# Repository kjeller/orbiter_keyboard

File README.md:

# Orbiter Keyboard

A 52-key split keyboard.

!!DISCLAIMER!! There are issues with v1.00 that needs manual patching:
- BOOT0 logic is reversed which makes device always go into DFU mode, R6 needs to be connected to GND
- USB-C CC pin pull-up is common, which makes the USB cable one-way, CC1 and CC2 each needs a 5.1k pull-down resistor

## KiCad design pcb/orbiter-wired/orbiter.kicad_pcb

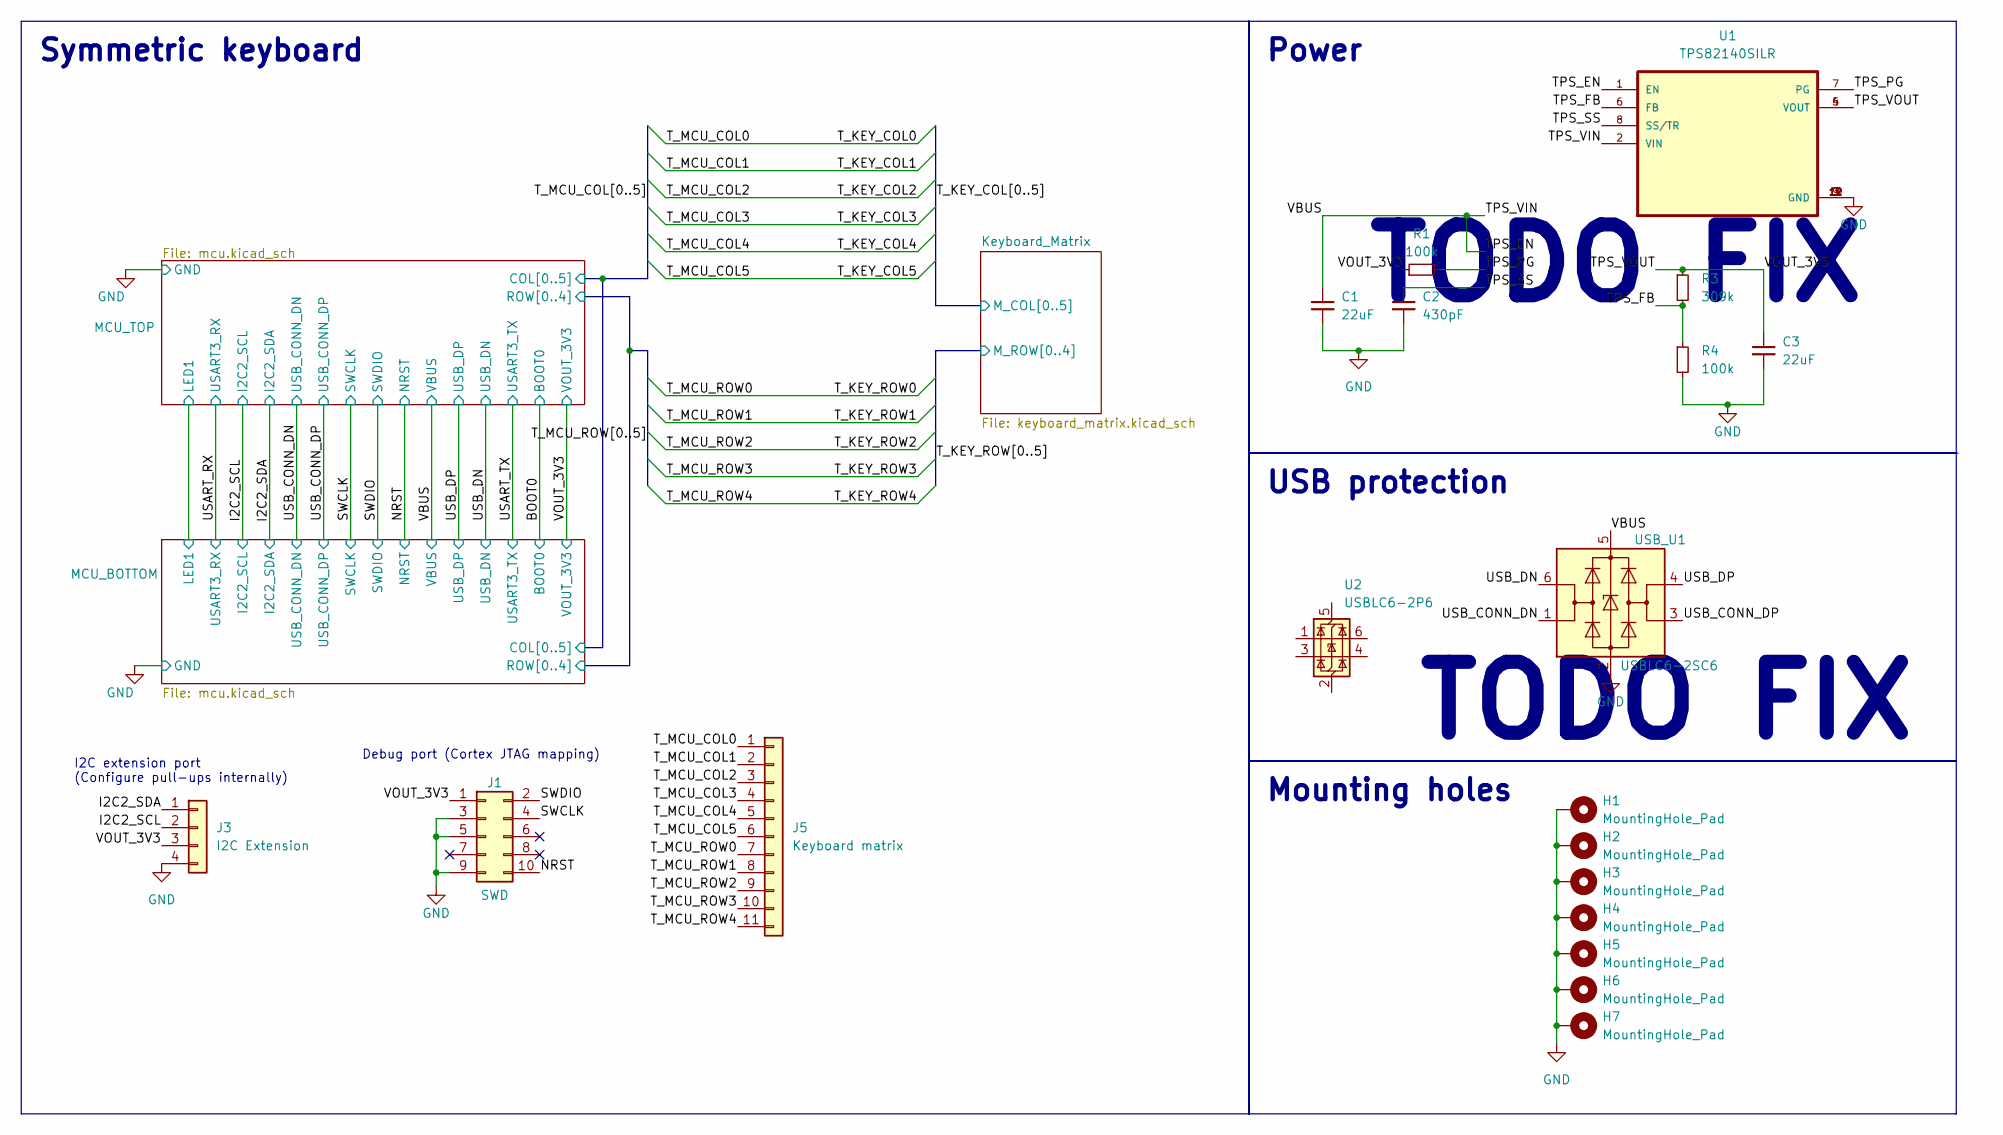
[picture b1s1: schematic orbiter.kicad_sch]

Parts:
C1, C3: 22uF; C_0603_1608Metric_Pad1.08x0.95mm_HandSolder; LCSC C59461
C2: 430pF; C_0603_1608Metric_Pad1.08x0.95mm_HandSolder; LCSC C1620
H1, H2, H3, H4, H5, H6, H7: MountingHole_Pad; MountingHole_2.7mm_M2.5_DIN965_Pad_reversible
J1: SWD; PinSocket_2x05_P2.54mm_Vertical
J3: I2C Extension; PinSocket_1x04_P2.54mm_Vertical
J5: Keyboard matrix; PinSocket_1x11_P2.54mm_Vertical
R1, R4: 100k; R_0603_1608Metric; LCSC C25803
R3: 309k; R_0603_1608Metric; LCSC C23024
U1: TPS82140SILR; LCSC C544385
U2: USBLC6-2P6; SOT-666
USB_U1: USBLC6-2SC6; SOT-23-6; LCSC C2687116

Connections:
/I2C2_SCL: J3.2; also elsewhere on the board
/I2C2_SDA: J3.1; also elsewhere on the board
/NRST: J1.10; also elsewhere on the board
/SWCLK: J1.4; also elsewhere on the board
/SWDIO: J1.2; also elsewhere on the board
/TPS_EN: C1.1, U1.1 (EN), U1.2 (VIN), USB_U1.5 (VBUS); also elsewhere on the board
/TPS_FB: R3.2, R4.1, U1.6 (FB)
/TPS_PG: R1.2, U1.7 (PG)
/TPS_SS: C2.1, U1.8 (SS/TR)
/TPS_VOUT: C3.1, J1.1, J3.3, R1.1, R3.1, U1.4 (VOUT), U1.5 (VOUT); also elsewhere on the board
/T_KEY_COL0: J5.1; also elsewhere on the board
/T_KEY_COL1: J5.2; also elsewhere on the board
/T_KEY_COL2: J5.3; also elsewhere on the board
/T_KEY_COL3: J5.4; also elsewhere on the board
/T_KEY_COL4: J5.5; also elsewhere on the board
/T_KEY_COL5: J5.6; also elsewhere on the board
/T_KEY_ROW0: J5.7; also elsewhere on the board
/T_KEY_ROW1: J5.8; also elsewhere on the board
/T_KEY_ROW2: J5.9; also elsewhere on the board
/T_KEY_ROW3: J5.10; also elsewhere on the board
/T_KEY_ROW4: J5.11; also elsewhere on the board
/USB_CONN_DN: USB_U1.1 (I/O1); also elsewhere on the board
/USB_CONN_DP: USB_U1.3 (I/O2); also elsewhere on the board
/USB_DN: USB_U1.6 (I/O1); also elsewhere on the board
/USB_DP: USB_U1.4 (I/O2); also elsewhere on the board
GND: C1.2, C2.2, C3.2, H1.1, H2.1, H3.1, H4.1, H5.1, H6.1, H7.1, J1.3, J1.5, J1.9, J3.4, R4.2, U1.3 (GND), U1.9 (GND), U1.10 (GND), U1.11 (GND), U1.12 (GND), USB_U1.2 (GND); also elsewhere on the board

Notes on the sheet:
TODO FIX
I2C extension port (Configure pull-ups internally)
Debug port (Cortex JTAG mapping)
Power
Symmetric keyboard
Mounting holes
USB protection

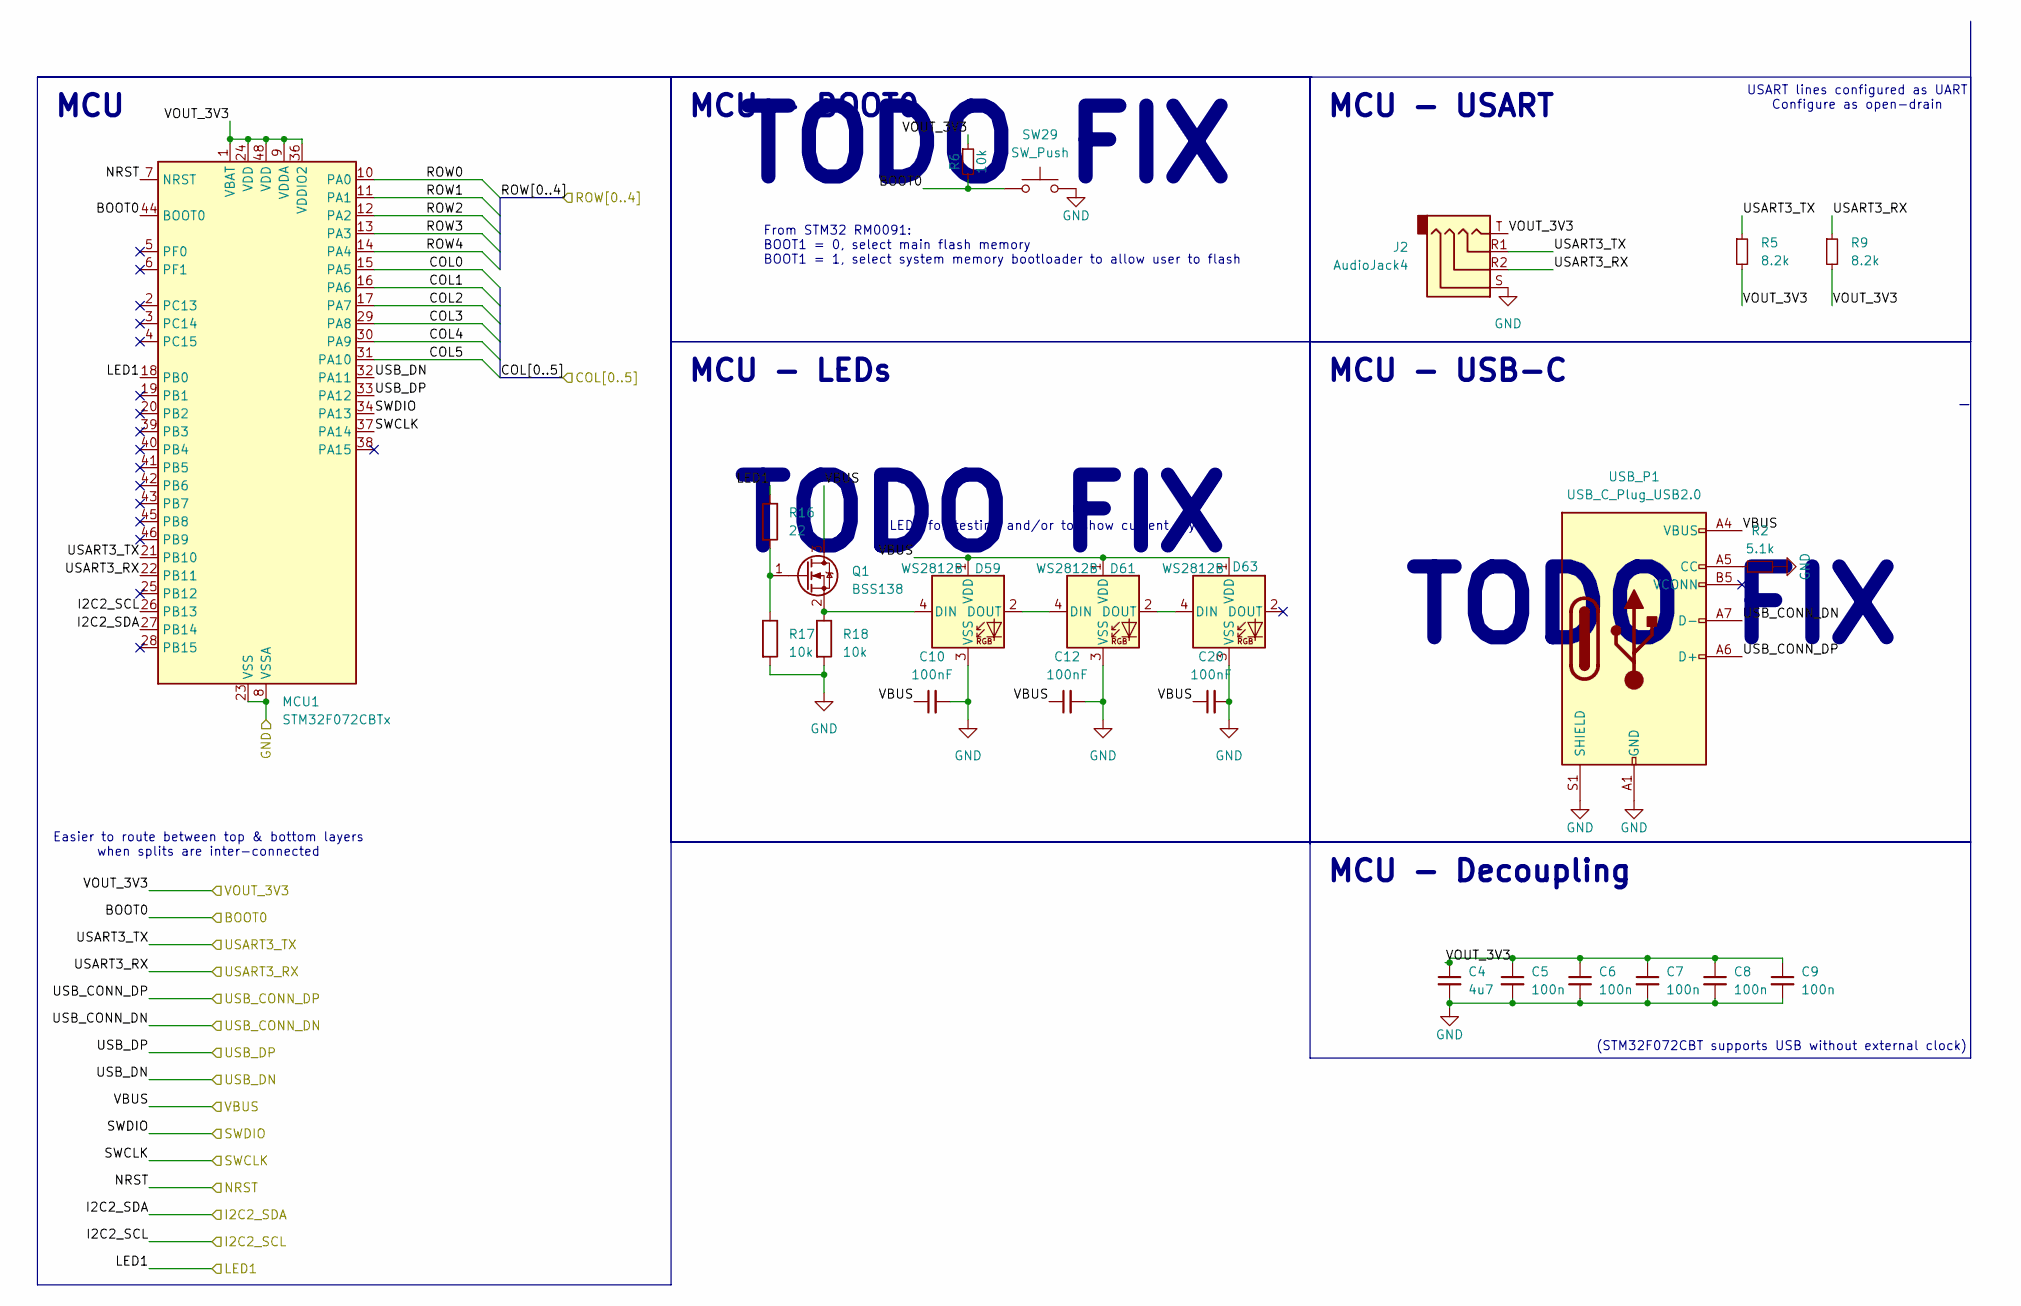
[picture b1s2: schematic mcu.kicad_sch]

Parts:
C4: 4u7; C_0603_1608Metric_Pad1.08x0.95mm_HandSolder
C5, C6, C7, C8, C9: 100n; C_0603_1608Metric_Pad1.08x0.95mm_HandSolder
C10, C12, C20: 100nF; C_0603_1608Metric_Pad1.08x0.95mm_HandSolder
D59, D61, D63: WS2812B; LED_WS2812B-2020_PLCC4_2.0x2.0mm
J2: AudioJack4; Jack_3.5mm_PJ320D_Horizontal
MCU1: STM32F072CBTx; LQFP-48_7x7mm_P0.5mm
Q1: BSS138; SOT-23; MPN BSS138
R2: 5.1k; R_0603_1608Metric
R5, R9: 8.2k; R_0603_1608Metric
R6, R17, R18: 10k; R_0603_1608Metric
R16: 22; R_0603_1608Metric
SW29: SW_Push; SW_SPST_PTS647_Sx38
USB_P1: USB_C_Plug_USB2.0; USB_C_Receptacle_XKB_U262-16XN-4BVC11

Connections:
/BOOT0: MCU1.44 (BOOT0), R6.2, SW29.1; also elsewhere on the board
/I2C2_SCL: MCU1.26 (PB13); also elsewhere on the board
/I2C2_SDA: MCU1.27 (PB14); also elsewhere on the board
/MCU_BOTTOM/LED1: MCU1.18 (PB0), R16.1; also elsewhere on the board
/NRST: MCU1.7 (NRST); also elsewhere on the board
/SWCLK: MCU1.37 (PA14); also elsewhere on the board
/SWDIO: MCU1.34 (PA13); also elsewhere on the board
/TPS_EN: C10.1, C12.1, C20.1, D59.1 (VDD), D61.1 (VDD), D63.1 (VDD), Q1.3 (D), USB_P1.A4 (VBUS), USB_P1.A9 (VBUS), USB_P1.B4 (VBUS), USB_P1.B9 (VBUS); also elsewhere on the board
/TPS_VOUT: C4.1, C5.1, C6.1, C7.1, C8.1, C9.1, J2.T, MCU1.1 (VBAT), MCU1.9 (VDDA), MCU1.24 (VDD), MCU1.36 (VDDIO2), MCU1.48 (VDD), R5.2, R6.1, R9.2; also elsewhere on the board
/T_KEY_COL0: MCU1.15 (PA5); also elsewhere on the board
/T_KEY_COL1: MCU1.16 (PA6); also elsewhere on the board
/T_KEY_COL2: MCU1.17 (PA7); also elsewhere on the board
/T_KEY_COL3: MCU1.29 (PA8); also elsewhere on the board
/T_KEY_COL4: MCU1.30 (PA9); also elsewhere on the board
/T_KEY_COL5: MCU1.31 (PA10); also elsewhere on the board
/T_KEY_ROW0: MCU1.10 (PA0); also elsewhere on the board
/T_KEY_ROW1: MCU1.11 (PA1); also elsewhere on the board
/T_KEY_ROW2: MCU1.12 (PA2); also elsewhere on the board
/T_KEY_ROW3: MCU1.13 (PA3); also elsewhere on the board
/T_KEY_ROW4: MCU1.14 (PA4); also elsewhere on the board
/USART_RX: J2.R2, MCU1.22 (PB11), R9.1; also elsewhere on the board
/USART_TX: J2.R1, MCU1.21 (PB10), R5.1; also elsewhere on the board
/USB_CONN_DN: USB_P1.A7 (D-); also elsewhere on the board
/USB_CONN_DP: USB_P1.A6 (D+); also elsewhere on the board
/USB_DN: MCU1.32 (PA11); also elsewhere on the board
/USB_DP: MCU1.33 (PA12); also elsewhere on the board
GND: C4.2, C5.2, C6.2, C7.2, C8.2, C9.2, C10.2, C12.2, C20.2, D59.3 (VSS), D61.3 (VSS), D63.3 (VSS), J2.S, MCU1.8 (VSSA), MCU1.23 (VSS), MCU1.35 (VSS), MCU1.47 (VSS), R2.2, R17.2, R18.2, SW29.2, USB_P1.A1 (GND), USB_P1.A12 (GND), USB_P1.B1 (GND), USB_P1.B12 (GND), USB_P1.S1 (SHIELD); also elsewhere on the board
unnamed: D59.4 (DIN), Q1.2 (S), R18.1
unnamed: D59.2 (DOUT), D61.4 (DIN)
unnamed: D61.2 (DOUT), D63.4 (DIN)
unnamed: Q1.1 (G), R16.2, R17.1
unnamed: R2.1, USB_P1.A5 (CC)

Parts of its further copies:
C11, C19, C21: 100nF; C_0603_1608Metric_Pad1.08x0.95mm_HandSolder
C13: 4u7; C_0603_1608Metric_Pad1.08x0.95mm_HandSolder
C14, C15, C16, C17, C18: 100n; C_0603_1608Metric_Pad1.08x0.95mm_HandSolder
D60, D62, D64: WS2812B; LED_WS2812B-2020_PLCC4_2.0x2.0mm
J4: AudioJack4; Jack_3.5mm_PJ320D_Horizontal
MCU2: STM32F072CBTx; LQFP-48_7x7mm_P0.5mm
Q2: BSS138; SOT-23; MPN BSS138
R7, R20, R21: 10k; R_0603_1608Metric
R8: 5.1k; R_0603_1608Metric
R10, R11: 8.2k; R_0603_1608Metric
R19: 22; R_0603_1608Metric
SW30: SW_Push; SW_SPST_PTS647_Sx38
USB_P2: USB_C_Plug_USB2.0; USB_C_Receptacle_XKB_U262-16XN-4BVC11

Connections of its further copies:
/BOOT0: MCU2.44 (BOOT0), R7.2, SW30.1; also elsewhere on the board
/I2C2_SCL: MCU2.26 (PB13); also elsewhere on the board
/I2C2_SDA: MCU2.27 (PB14); also elsewhere on the board
/MCU_BOTTOM/LED1: MCU2.18 (PB0), R19.1; also elsewhere on the board
/NRST: MCU2.7 (NRST); also elsewhere on the board
/SWCLK: MCU2.37 (PA14); also elsewhere on the board
/SWDIO: MCU2.34 (PA13); also elsewhere on the board
/TPS_EN: C11.1, C19.1, C21.1, D60.1 (VDD), D62.1 (VDD), D64.1 (VDD), Q2.3 (D), USB_P2.A4 (VBUS), USB_P2.A9 (VBUS), USB_P2.B4 (VBUS), USB_P2.B9 (VBUS); also elsewhere on the board
/TPS_VOUT: C13.1, C14.1, C15.1, C16.1, C17.1, C18.1, J4.T, MCU2.1 (VBAT), MCU2.9 (VDDA), MCU2.24 (VDD), MCU2.36 (VDDIO2), MCU2.48 (VDD), R7.1, R10.2, R11.2; also elsewhere on the board
/T_KEY_COL0: MCU2.15 (PA5); also elsewhere on the board
/T_KEY_COL1: MCU2.16 (PA6); also elsewhere on the board
/T_KEY_COL2: MCU2.17 (PA7); also elsewhere on the board
/T_KEY_COL3: MCU2.29 (PA8); also elsewhere on the board
/T_KEY_COL4: MCU2.30 (PA9); also elsewhere on the board
/T_KEY_COL5: MCU2.31 (PA10); also elsewhere on the board
/T_KEY_ROW0: MCU2.10 (PA0); also elsewhere on the board
/T_KEY_ROW1: MCU2.11 (PA1); also elsewhere on the board
/T_KEY_ROW2: MCU2.12 (PA2); also elsewhere on the board
/T_KEY_ROW3: MCU2.13 (PA3); also elsewhere on the board
/T_KEY_ROW4: MCU2.14 (PA4); also elsewhere on the board
/USART_RX: J4.R2, MCU2.22 (PB11), R10.1; also elsewhere on the board
/USART_TX: J4.R1, MCU2.21 (PB10), R11.1; also elsewhere on the board
/USB_CONN_DN: USB_P2.A7 (D-); also elsewhere on the board
/USB_CONN_DP: USB_P2.A6 (D+); also elsewhere on the board
/USB_DN: MCU2.32 (PA11); also elsewhere on the board
/USB_DP: MCU2.33 (PA12); also elsewhere on the board
GND: C11.2, C13.2, C14.2, C15.2, C16.2, C17.2, C18.2, C19.2, C21.2, D60.3 (VSS), D62.3 (VSS), D64.3 (VSS), J4.S, MCU2.8 (VSSA), MCU2.23 (VSS), MCU2.35 (VSS), MCU2.47 (VSS), R8.2, R20.2, R21.2, SW30.2, USB_P2.A1 (GND), USB_P2.A12 (GND), USB_P2.B1 (GND), USB_P2.B12 (GND), USB_P2.S1 (SHIELD); also elsewhere on the board
unnamed: D60.4 (DIN), Q2.2 (S), R21.1
unnamed: D60.2 (DOUT), D62.4 (DIN)
unnamed: D62.2 (DOUT), D64.4 (DIN)
unnamed: Q2.1 (G), R19.2, R20.1
unnamed: R8.1, USB_P2.A5 (CC)

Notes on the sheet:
TODO FIX
From STM32 RM0091: BOOT1 = 0, select main flash memory BOOT1 = 1, select system memory bootloader to allow user to flash
LEDs for testing and/or to show current layer
Easier to route between top & bottom layers when splits are inter-connected
USART lines configured as UART Configure as open-drain
(STM32F072CBT supports USB without external clock)
MCU - LEDs
MCU - USART
MCU - BOOT0
MCU - Decoupling
MCU
MCU - USB-C

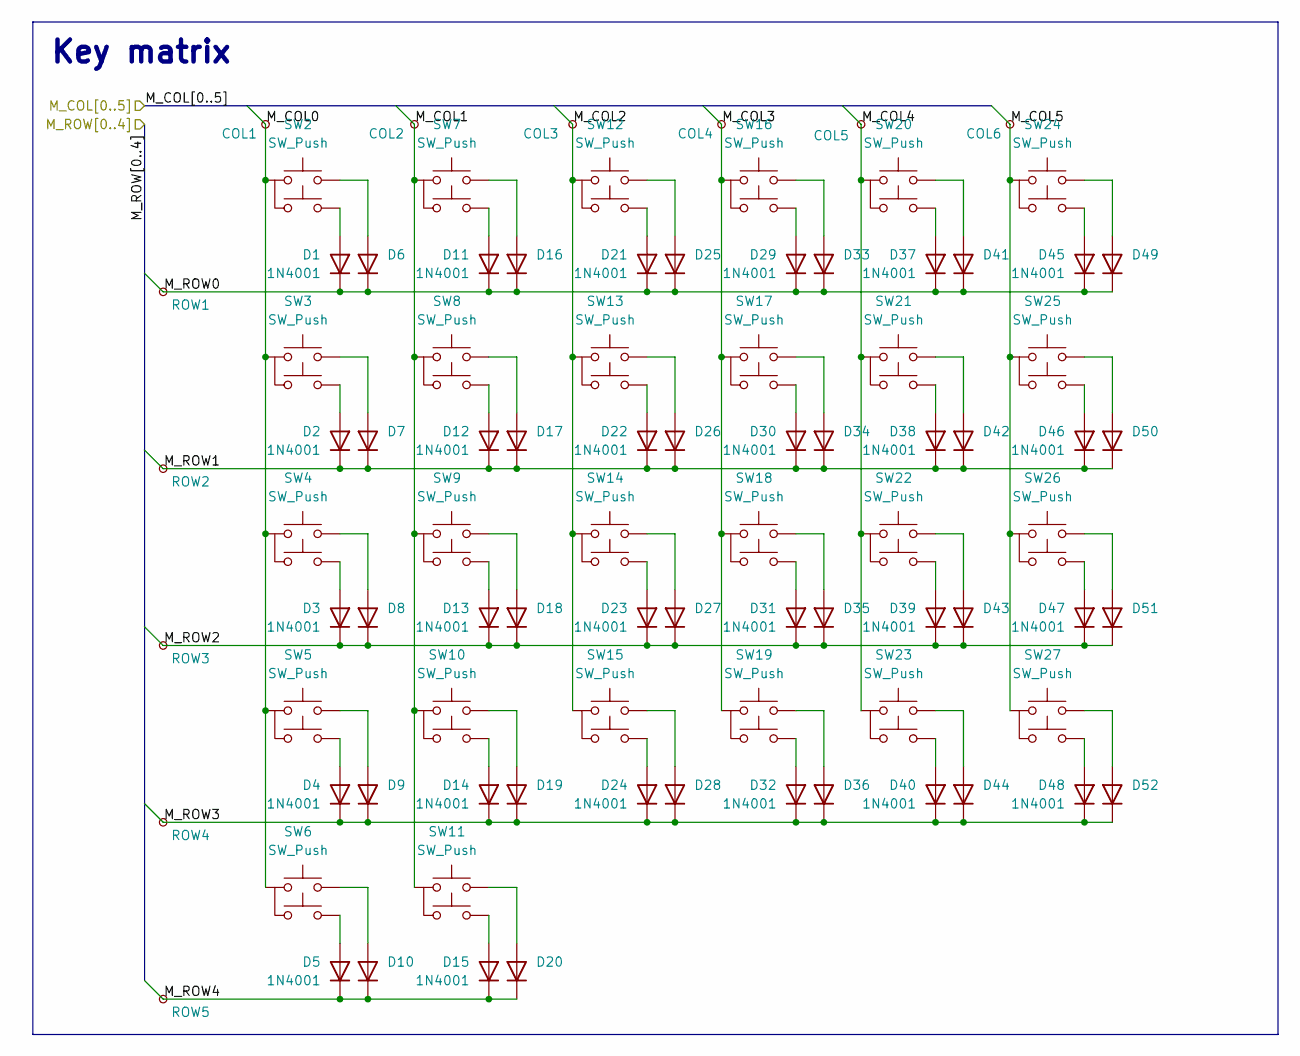
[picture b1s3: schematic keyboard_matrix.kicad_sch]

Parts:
COL1, COL2, COL3, COL4, COL5, COL6: TestPoint_Small; TestPoint_THTPad_D1.0mm_Drill0.5mm_reversible
D1, D2, D3, D4, D5, D6, D7, D8, D9, D10, D11, D12, D13, D14, D15, D16, D17, D18, D19, D20, D21, D22, D23, D24, D25, D26, D27, D28, D29, D30, D31, D32, D33, D34, D35, D36, D37, D38, D39, D40, D41, D42, D43, D44, D45, D46, D47, D48, D49, D50, D51, D52: 1N4001; D_SOD-323_HandSoldering
ROW1, ROW2, ROW3, ROW4, ROW5: TestPoint_Small; TestPoint_THTPad_D1.0mm_Drill0.5mm_reversible
SW2, SW3, SW4, SW5, SW6, SW7, SW8, SW9, SW10, SW11, SW12, SW13, SW14, SW15, SW16, SW17, SW18, SW19, SW20, SW21, SW22, SW23, SW24, SW25, SW26, SW27: SW_Push; SW_Kailh_Choc_V2_1.00u_Reversible

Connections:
/T_KEY_COL0: COL1.1, SW2.1, SW3.1, SW4.1, SW5.1, SW6.1; also elsewhere on the board
/T_KEY_COL1: COL2.1, SW7.1, SW8.1, SW9.1, SW10.1, SW11.1; also elsewhere on the board
/T_KEY_COL2: COL3.1, SW12.1, SW13.1, SW14.1, SW15.1; also elsewhere on the board
/T_KEY_COL3: COL4.1, SW16.1, SW17.1, SW18.1, SW19.1; also elsewhere on the board
/T_KEY_COL4: COL5.1, SW20.1, SW21.1, SW22.1, SW23.1; also elsewhere on the board
/T_KEY_COL5: COL6.1, SW24.1, SW25.1, SW26.1, SW27.1; also elsewhere on the board
/T_KEY_ROW0: D1.1 (K), D6.1 (K), D11.1 (K), D16.1 (K), D21.1 (K), D25.1 (K), D29.1 (K), D33.1 (K), D37.1 (K), D41.1 (K), D45.1 (K), D49.1 (K), ROW1.1; also elsewhere on the board
/T_KEY_ROW1: D2.1 (K), D7.1 (K), D12.1 (K), D17.1 (K), D22.1 (K), D26.1 (K), D30.1 (K), D34.1 (K), D38.1 (K), D42.1 (K), D46.1 (K), D50.1 (K), ROW2.1; also elsewhere on the board
/T_KEY_ROW2: D3.1 (K), D8.1 (K), D13.1 (K), D18.1 (K), D23.1 (K), D27.1 (K), D31.1 (K), D35.1 (K), D39.1 (K), D43.1 (K), D47.1 (K), D51.1 (K), ROW3.1; also elsewhere on the board
/T_KEY_ROW3: D4.1 (K), D9.1 (K), D14.1 (K), D19.1 (K), D24.1 (K), D28.1 (K), D32.1 (K), D36.1 (K), D40.1 (K), D44.1 (K), D48.1 (K), D52.1 (K), ROW4.1; also elsewhere on the board
/T_KEY_ROW4: D5.1 (K), D10.1 (K), D15.1 (K), D20.1 (K), ROW5.1; also elsewhere on the board
unnamed: D1.2 (A), SW2.3
unnamed: D2.2 (A), SW3.3
unnamed: D3.2 (A), SW4.3
unnamed: D4.2 (A), SW5.3
unnamed: D5.2 (A), SW6.3
unnamed: D6.2 (A), SW2.2
unnamed: D7.2 (A), SW3.2
unnamed: D8.2 (A), SW4.2
unnamed: D9.2 (A), SW5.2
unnamed: D10.2 (A), SW6.2
unnamed: D11.2 (A), SW7.3
unnamed: D12.2 (A), SW8.3
unnamed: D13.2 (A), SW9.3
unnamed: D14.2 (A), SW10.3
unnamed: D15.2 (A), SW11.3
unnamed: D16.2 (A), SW7.2
unnamed: D17.2 (A), SW8.2
unnamed: D18.2 (A), SW9.2
unnamed: D19.2 (A), SW10.2
unnamed: D20.2 (A), SW11.2
unnamed: D21.2 (A), SW12.3
unnamed: D22.2 (A), SW13.3
unnamed: D23.2 (A), SW14.3
unnamed: D24.2 (A), SW15.3
unnamed: D25.2 (A), SW12.2
unnamed: D26.2 (A), SW13.2
unnamed: D27.2 (A), SW14.2
unnamed: D28.2 (A), SW15.2
unnamed: D29.2 (A), SW16.3
unnamed: D30.2 (A), SW17.3
unnamed: D31.2 (A), SW18.3
unnamed: D32.2 (A), SW19.3
unnamed: D33.2 (A), SW16.2
unnamed: D34.2 (A), SW17.2
unnamed: D35.2 (A), SW18.2
unnamed: D36.2 (A), SW19.2
unnamed: D37.2 (A), SW20.3
unnamed: D38.2 (A), SW21.3
unnamed: D39.2 (A), SW22.3
unnamed: D40.2 (A), SW23.3
unnamed: D41.2 (A), SW20.2
unnamed: D42.2 (A), SW21.2
unnamed: D43.2 (A), SW22.2
unnamed: D44.2 (A), SW23.2
unnamed: D45.2 (A), SW24.3
unnamed: D46.2 (A), SW25.3
unnamed: D47.2 (A), SW26.3
unnamed: D48.2 (A), SW27.3
unnamed: D49.2 (A), SW24.2
unnamed: D50.2 (A), SW25.2
unnamed: D51.2 (A), SW26.2
unnamed: D52.2 (A), SW27.2

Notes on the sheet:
Key matrix

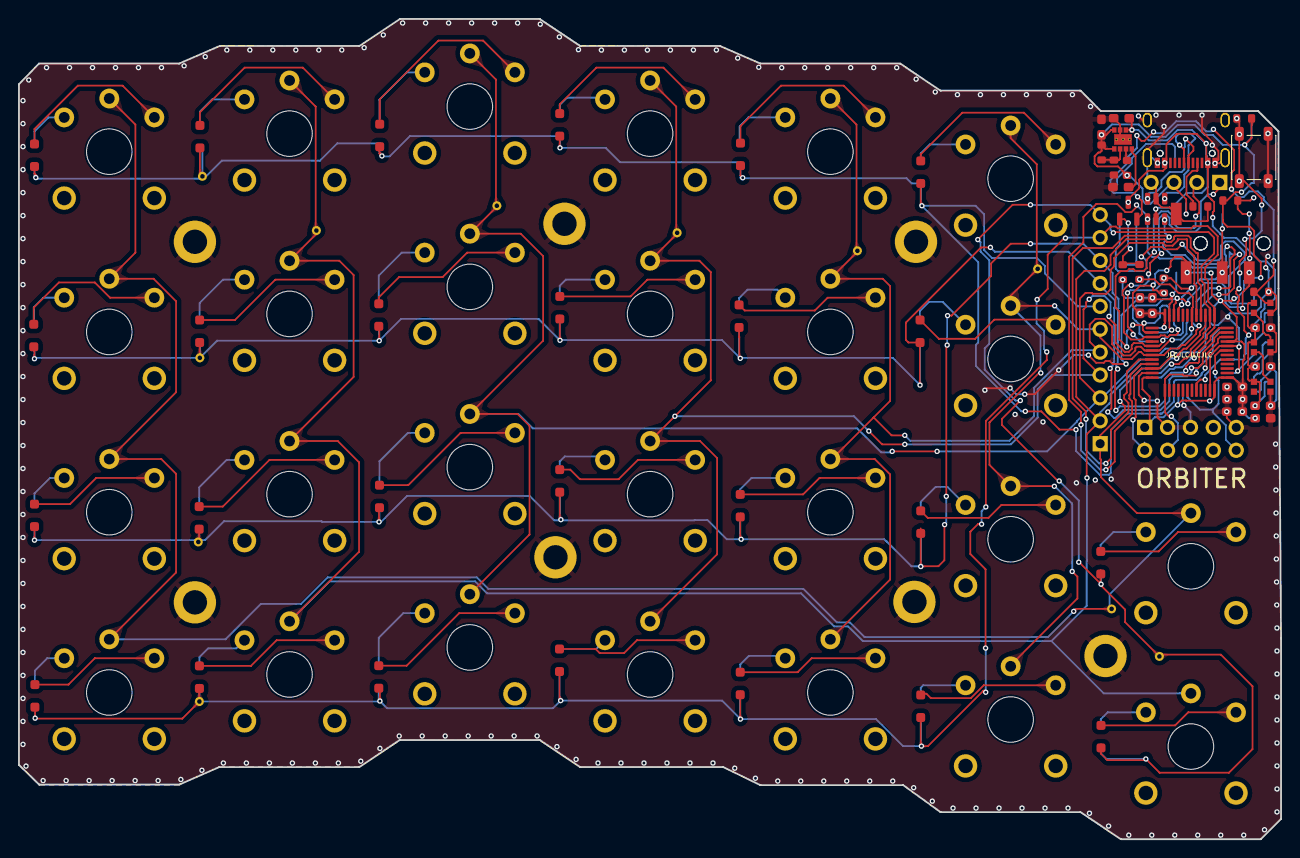
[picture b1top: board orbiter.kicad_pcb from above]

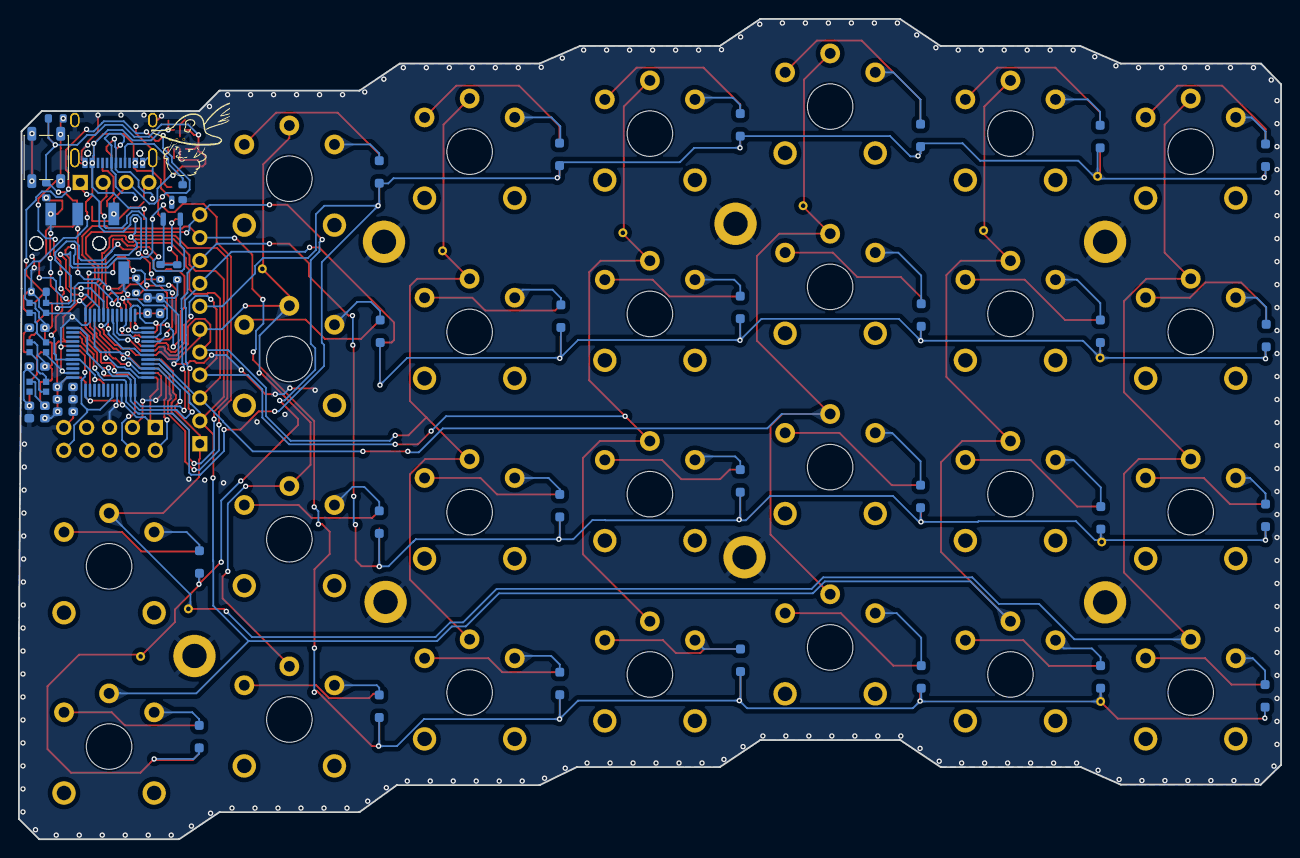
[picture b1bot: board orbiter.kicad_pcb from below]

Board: 2 copper layers, 140.0 x 91.0 mm, 155 parts (50 on the bottom side), 92 nets.

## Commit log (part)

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2024-05-07 Add BOOT0 handling and start working on power schematics
2024-05-08 Start adding USB C connector circuit
2024-05-10 Temp placement of switches and usb circuitry
2024-05-10 Fix issue with sw push dual footprint
2024-05-10 Add step down circuit in schematic editor
2024-06-02 Add PCB fonts
2024-06-02 Continue placing components for USB
2024-06-04 Rotate Kailh 3D model to be correctly aligned
2024-06-04 Fix flipped switch
2024-06-04 Add pull down for USB CC
2024-06-04 Add colors to STEP Kailh switch
2024-06-05 Add folder for step files
    Add PJ-320B step file
2024-06-05 Add TRRS connector for serial communication between splits
2024-06-06 Move step files to step folder
    Add step file for USB C jack
2024-06-06 Prel. placement of all components
2024-06-06 Add step down step file
2024-06-06 WIP 0 errors, 58 warnings
2024-06-06 Fix issue with duplicate edge cut
2024-06-07 Latest
2024-06-09 Add smaller logo
2024-06-09 Cleanup routes and remove all silk
2024-06-09 More cleanup
2024-06-10 Add dxf file for edge cut
2024-06-10 Update gitignore
2024-06-10 GND copper fill zone now aligned with edge cut
    Move USB port closer to edge
2024-06-10 Add via stitching around edge
2024-06-10 Add JLPCB part numbers
2024-06-10 Add JLCPCB hide text in silk
2024-06-10 Replace temp project name with orbiter
2024-06-10 Adjust folder name slightly
2024-06-10 Add crude version text
2024-06-10 Use jlcpcb addon for db handling for BOM
2024-06-10 Latest schematic
2024-06-10 Move diodes away from kb switch
2024-06-10 Orbiter wired v1.0 gerber & cleanup of old project files
2024-06-11 Change diode footprints 0603 -> SOD-323
2024-06-11 Move symbols into their own folder
    Add footprint and symbol for TPS82140SILR that is correct size
2024-06-11 Put all diodes on respective side
2024-06-11 Add step file for TPS
2024-06-17 WIP prepare component placement for standalone dev pcb
2024-06-23 Latest WIP
2024-06-27 No DRC errors with new clean layout
2024-06-27 Add pull-up for UART RX as well
2024-06-27 Add via stitching and graphics on front silk back
2024-06-29 Remove unused production files
2024-06-29 Edit project files to prepare for manufacturing
2024-06-29 Set PCB version v1.00
2025-02-02 Add JLPCB plugin generated files to gitignore
2025-02-02 Add TODOs for fixes for next version
2025-02-02 Update paths to use kicad-library submodule
2025-02-02 Remove unused libraries from library migration
